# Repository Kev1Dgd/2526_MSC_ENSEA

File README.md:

# 🛠️ 2526_MSC_ENSEA — Travaux Pratiques & Projet de 3ᵉ Année

## 👋 Présentation

Bienvenue sur le dépôt GitHub regroupant **l’ensemble des travaux pratiques (TP)** et **le projet de 3ᵉ année** réalisés dans le cadre de la formation à l’[**École Nationale Supérieure de l’Électronique et de ses Applications (ENSEA)**](https://www.ensea.fr/).

Ce dépôt est maintenu par :

* **Kévin Dgd** ([Kev1Dgd](https://github.com/Kev1Dgd))
* **Elio Flandin** ([elioflandin](https://github.com/elioflandin))
* **Tristan Noterman** (projet)

---

## 🎓 Contexte académique

Nous sommes actuellement en **troisième année de la spécialité *Mécatronique et Systèmes Complexes (MSC)*** à l’ENSEA.
Cette spécialité forme des ingénieurs capables de concevoir, modéliser et piloter des systèmes intégrant à la fois des composants **mécaniques, électroniques et informatiques embarqués**.

### 🧩 Matières étudiées

Les TP et projets s’appuient sur les enseignements suivants :

* 🤖 **Robotique**
* 📡 **Capteurs et chaînes de mesure**
* 🧠 **Systèmes d’acquisition et de commande**
* ⏱️ **Noyau temps réel**
* 🔗 **Bus et réseaux**
* ✈️ **Préparation d'un drone volant à "l'infini"**

---

## 📂 Structure du dépôt

```
📦 2526_MSC_ENSEA
 ┣ 📁 Robotique_TP
 ┣ 📁 Capteurs_TP
 ┣ 📁 SystemesAcquisitionCommande_TP
 ┣ 📁 Noyau_Temps_Reel_TP
 ┣ 📁 Bus&Reseaux_TP
 ┣ 📁 Projet_Drone_Infini
 ┗ 📜 README.md
```

Chaque dossier de TP contient :

* Le code source (`.c`, `.cpp`, `.py`, `.ino`, etc.)
* Les schémas électriques / mécaniques associés
* Les rapports ou notes explicatives

---

## 🛩️ Projet de 3ᵉ année — **Planeur Énergétiquement Autonome**

### 🧠 Objectif du projet

Concevoir un **planeur miniature autonome** capable de :

* **Voler indéfiniment** sans intervention extérieure
* **Exploiter l’énergie solaire** le jour pour recharger ses batteries
* **Utiliser un moteur électrique** la nuit pour reprendre de l’altitude

### ⚙️ Aspects techniques couverts

* **Conception électronique complète (PCB)**
* **Développement embarqué (microcontrôleur, C/C++)**
* **Asservissement et contrôle en vol**
* **Gestion énergétique et supervision logicielle**

### 🧰 Technologies utilisées

* Conception PCB : *KiCad / Altium Designer*
* Microcontrôleur : *STM32 / Arduino / ESP32 (selon choix final)*
* Simulation / modélisation : *MATLAB / Simulink*
* Communication : *Bus CAN, UART, I²C*
* Langages : *C, Python, Assembly (au besoin)*

---

## 🧑‍🤝‍🧑 Équipe projet

| Nom                  | Rôle                                          | GitHub                                         |
| -------------------- | --------------------------------------------- | ---------------------------------------------- |
| **Kévin Dgd**        | Développement, intégration et électronique    | [@Kev1Dgd](https://github.com/Kev1Dgd)         |
| **Elio Flandin**     | Programmation, conception système, tests      | [@elioflandin](https://github.com/elioflandin) |
| **Tristan Noterman** | Modélisation, simulation et support technique | —                                              |

---

## 🚀 Objectif final

Créer un **système mécatronique complet**, modulaire et documenté, combinant :

* électronique embarquée,
* asservissement moteur,
* gestion énergétique intelligente,
* et communication robuste.

Le tout dans le cadre d’un **projet d’ingénierie complet**, fidèle à la démarche et aux exigences de la formation ENSEA.

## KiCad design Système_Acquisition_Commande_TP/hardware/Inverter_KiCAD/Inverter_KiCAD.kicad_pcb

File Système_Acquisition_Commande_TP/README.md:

# 🏎️ Projet MSC : Asservissement de Machine à Courant Continu (MCC)
**ENSEA 2025-2026** DUGARD Kevin & FLANDIN Elio  
**Encadrant :** Nicolas Papazoglou

---

## 📌 Présentation du Projet
Ce projet consiste à réaliser le pilotage complet d'un moteur à courant continu via un **hacheur en pont en H** et une carte **Nucleo-STM32G474RE**. 

L'objectif est d'implémenter :
1. La génération de signaux **PWM complémentaires décalés**.
2. L'acquisition de données capteurs (courant, vitesse).
3. L'asservissement en temps réel du système.

---

## 🛠️ Architecture du Logiciel
Le projet est structuré de manière modulaire pour faciliter la maintenance et la portabilité :

* **`acquisition/`** : Gestion des entrées analogiques (ADC/DMA) et des codeurs incrémentaux.
* **`motor_control/`** : Pilotage du hacheur (PWM) et algorithmes d'asservissement (PID).
* **`user_interface/`** : Interaction via le `shell` UART, gestion des LEDs et boutons.
* **`app.c`** : Point d'entrée de l'application (initialisation et boucle principale).

---

## 🚀 Fonctionnalités du Shell
Nous utilisons un terminal série (115200 baud) pour piloter le moteur en temps réel.

| Commande | Action |
| :--- | :--- |
| `help` | Affiche la liste des commandes disponibles. |
| `start` | Active les PWM et fixe le rapport cyclique à 50% (repos). |
| `stop` | Désactive immédiatement les sorties PWM. |
| `speed <val>` | Définit la vitesse cible avec une rampe d'accélération. |
| `test` | Vérifie la transmission des arguments. |

---

## 📈 État d'avancement du TP

### 1. Commande Basique (PWM)
- [x] Configuration du Timer à **20kHz**.
- [x] Insertion du **temps mort** (Deadtime) selon la datasheet.
- [x] Validation à l'oscilloscope des signaux complémentaires.
- [x] Implémentation de la rampe d'accélération pour éviter les pics de courant.

### 2. Acquisition de Données
- [ ] Mesure du courant par **ADC en mode DMA** (synchrone avec la PWM).
- [ ] Lecture de la vitesse via le **codeur incrémental**.
- [ ] Calcul de la fonction de transfert du capteur de vitesse.

### 3. Asservissement (En cours...)
- [ ] Identification de la constante de temps mécanique.
- [ ] Implémentation du correcteur PID.

---

## 🛠 Configuration Matérielle (Hardware)

### Hacheur & PWM
* **Fréquence :** 20 kHz
* **Résolution :** > 10 bits
* **Topologie :** Commande complémentaire décalée (4 transistors).

---

## 📝 Bonnes Pratiques de Code
Pour ce projet, nous respectons les règles suivantes :
* **Naming :** `snake_case` pour les variables, `UPPER_CASE` pour les macros.
* **Zéro "Nombre Magique" :** Utilisation systématique de `#define`.
* **Sécurité :** Vérification systématique du retour des fonctions HAL.
* **Modularité :** Fonctions factorisées pour éviter la duplication.

---

## ⚙️ Installation et Utilisation
1. Cloner le dépôt :
   ```bash
   git clone [https://github.com/votre_nom/2526_MSC_SAC_NOM1_NOM2.git](https://github.com/votre_nom/2526_MSC_SAC_NOM1_NOM2.git)

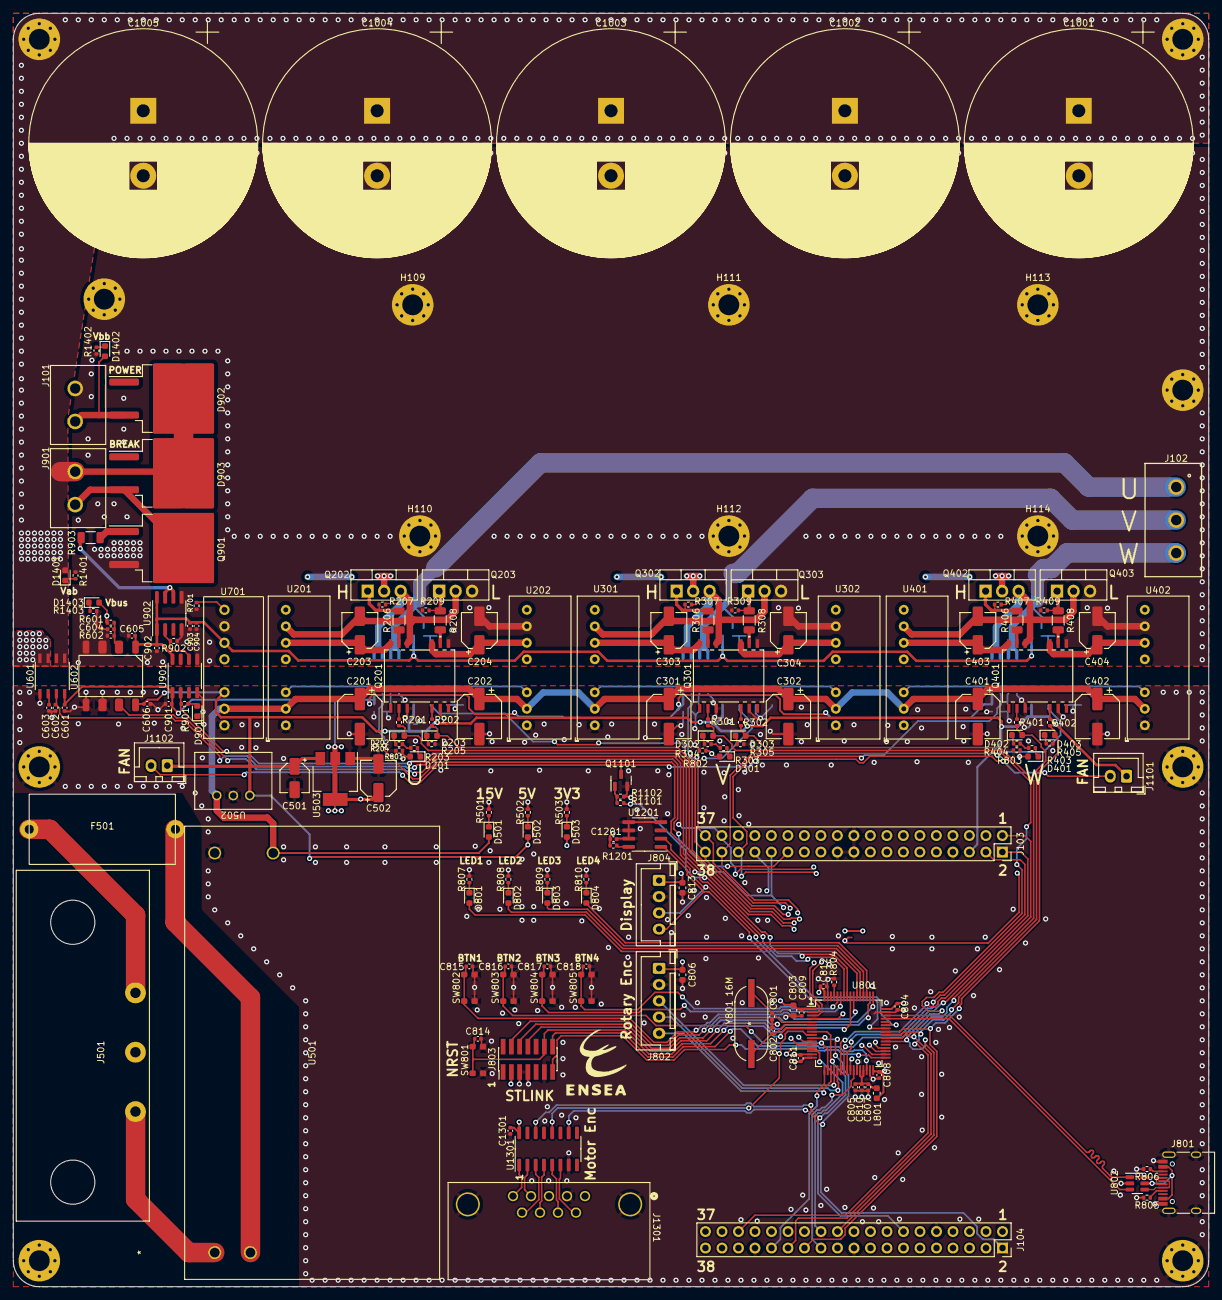
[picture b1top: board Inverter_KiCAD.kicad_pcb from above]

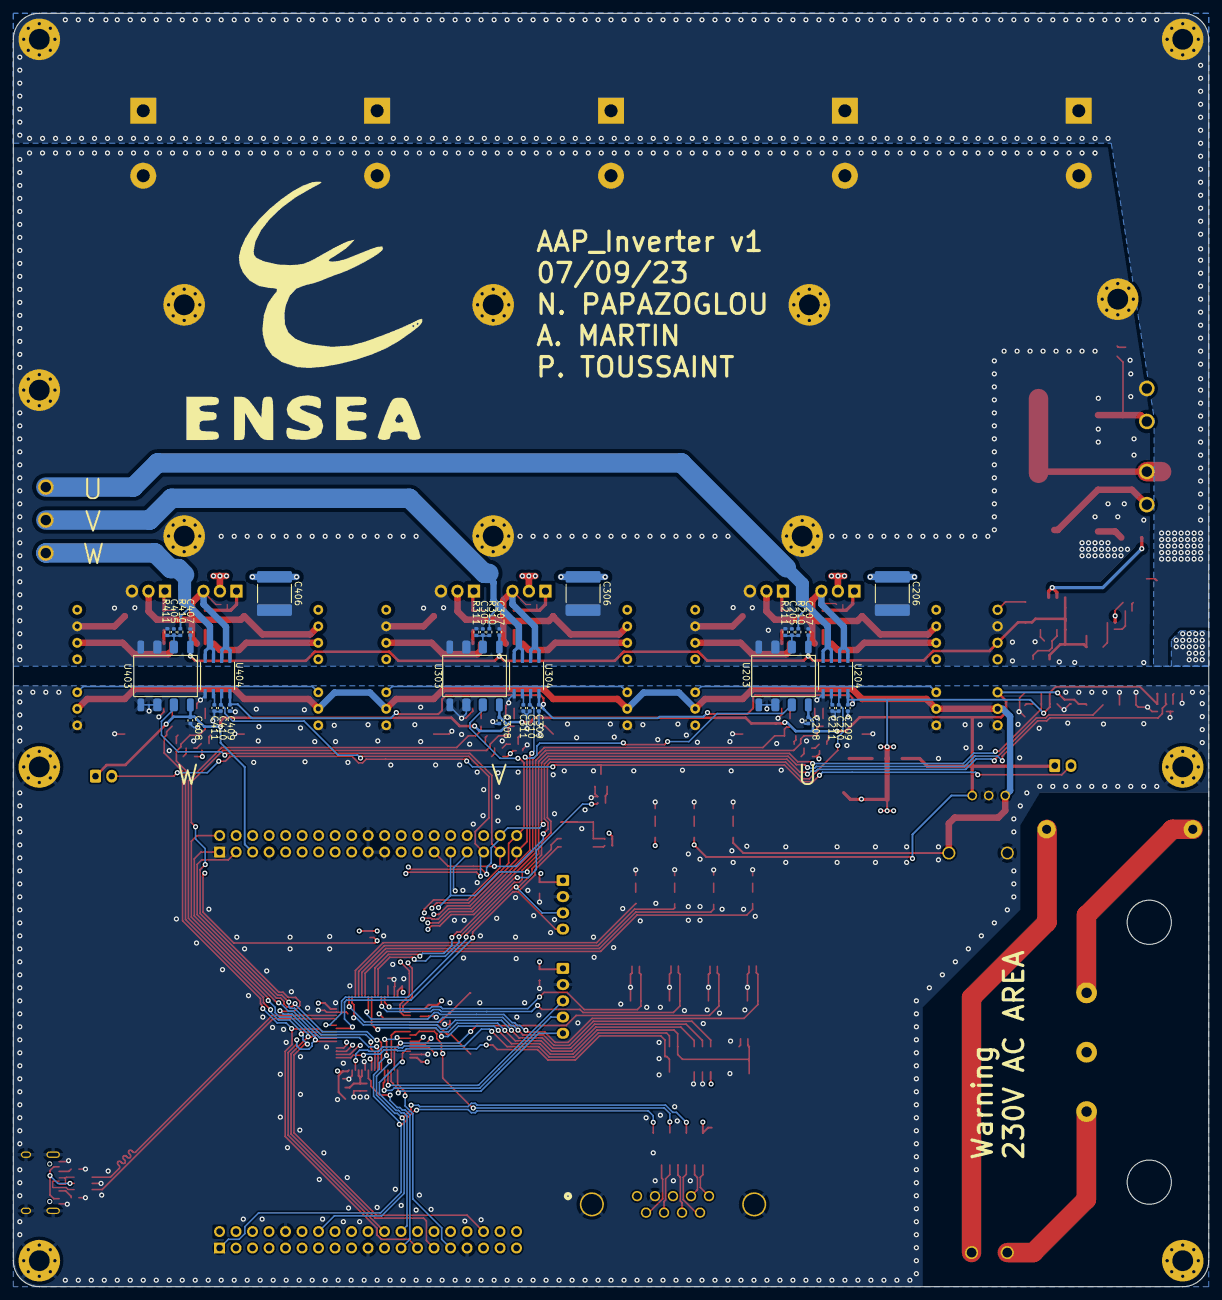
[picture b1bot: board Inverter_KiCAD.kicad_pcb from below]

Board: 4 copper layers, 184.0 x 196.0 mm, 220 parts (33 on the bottom side), 139 nets.

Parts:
C201, C202, C301, C302, C401, C402: 100u; CP_Elec_6.3x7.7
C203, C204, C303, C304, C403, C404, C502: 22u; CP_Elec_5x5.4
C205, C305, C405, C604: 10n; C_0402_1005Metric
C206, C306, C406: 10u; C_2220_5650Metric
C207, C208, C307, C308, C407, C408, C605, C606, C804, C807, C808, C809, C810, C811, C812, C814, C815, C816, C817, C818, C901, C902, C1201, C1301: 100n; C_0402_1005Metric
C209, C210, C211, C309, C310, C311, C409, C410, C411, C601, C602, C603: 4.7n; C_0402_1005Metric
C501: 10u; CP_Elec_4x5.4
C801, C802: 22p; C_0402_1005Metric
C803, C806, C813: 10u; C_0603_1608Metric
C805, C903: 1u; C_0402_1005Metric
C904: 1n; C_0402_1005Metric
C1001, C1002, C1003, C1004, C1005: 1.5m; CP_Radial_D35.0mm_P10.00mm_SnapIn
D201, D301, D401: Green LED; LED_0603_1608Metric
D202, D203, D302, D303, D402, D403, D501, D502, D503, D901, D1401, D1402, D1403: Red LED; LED_0603_1608Metric
D801, D802, D803, D804: Blue LED; LED_0603_1608Metric
D902, D903: VS-15TQ060S-M3; TO-263-2
F501: Fuse; 0031.8201
H101, H102, H103, H104, H105, H106, H107, H108, H109, H110, H111, H112, H113, H114: MountingHole_Pad; MountingHole_3.2mm_M3_Pad_Via
J101, J901: Conn_01x02; 691311500102
J102: Conn_01x03; 691311500103
J103, J104: Conn_02x19_Odd_Even; PinSocket_2x19_P2.54mm_Vertical
J501: PX0580-PC-12132
J801: USB_C_Receptacle_USB2.0; USB_C_Receptacle_HRO_TYPE-C-31-M-12
J802: Conn_01x05; JST_XH_B5B-XH-A_1x05_P2.50mm_Vertical
J803: Conn_ST_STDC14; PinHeader_2x07_P1.27mm_Vertical_SMD
J804: Conn_01x04; JST_XH_B4B-XH-A_1x04_P2.50mm_Vertical
J1101, J1102: Conn_01x02; JST_XH_B2B-XH-A_1x02_P2.50mm_Vertical
J1301: DE9_Receptacle_MountingHoles; 618009233821
L801: 39n; L_0603_1608Metric
Q201, Q301, Q401: HCPL-315J-500E; SO-16_HCPL-315J_BRA
Q202, Q203, Q302, Q303, Q402, Q403: IRF540N; TO-220-3_Vertical
Q901: BUK9637-100E; TO-263-2
Q1101: SQ2310ES; SOT-23
R201, R202, R301, R302, R401, R402: 170; R_0402_1005Metric
R203, R204, R205, R303, R304, R305, R403, R404, R405, R503, R807, R808, R809, R810, R901: 390; R_0402_1005Metric
R206, R208, R306, R308, R406, R408: 30; R_1206_3216Metric
R207, R209, R307, R309, R407, R409, R801, R802, R803, R804, R902, R1102, R1401, R1402, R1403: 10k; R_0402_1005Metric
R210, R310, R410, R601: 470k; R_0402_1005Metric
R211, R311, R411, R602: 1k; R_0402_1005Metric
R501: 2k7; R_0402_1005Metric
R502: 680; R_0402_1005Metric
R701: 27k; R_0402_1005Metric
R805, R806: 5.1k; R_0402_1005Metric
R903: 4.7; R_1206_3216Metric
R1101: 22; R_0402_1005Metric
R1201: 200; R_0402_1005Metric
SW801, SW802, SW803, SW804, SW805: SW_Push; 435451019820
U201, U202, U301, U302, U401, U402: MPRB2415S-6W; MPRB2415S
U203, U303, U403, U602: HCPL-7800-500E; DIP-8 Gull Wing
U204, U304, U404, U601: GO 10-SME/SP3; SOIC8-GO-SME&slash_SP3_LEM
U501: MP-LD30-23B12R2; MP-LD30-23B15R2
U502: 173010542; 173010578
U503: AZ1117-3.3; SOT-223-3_TabPin2
U701: 17791063215
U801: STM32G474RETx; LQFP-64_10x10mm_P0.5mm
U802: USBLC6-2SC6; SOT-23-6
U901: ACPL-077L; SO-8_3.9x4.9mm_P1.27mm
U902: TC1412; SOIC-8_3.9x4.9mm_P1.27mm
U1201: TCN75A; SOIC-8_3.9x4.9mm_P1.27mm
U1301: MAX3097ECSE+; SOIC-16_3.9x9.9mm_P1.27mm
Y801: 16M; ABLS-7.3728MHZ-CL-RESR-A-1-G-F

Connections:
/5V: C207.1, C307.1, C407.1, C605.1, C902.1, C903.1, C904.1, U203.1 (VDD1), U303.1 (VDD1), U403.1 (VDD1), U602.1 (VDD1), U701.6 (Vout), U901.8 (VDD2), U902.1 (VDD), U902.8 (VDD)
/Arm_IRF540NBbF1/ARM_OUT: C303.2, Q301.14 (VEE), Q302.3 (S), Q303.2 (D), R307.2, U301.7 (0V), U304.1 (IP+), U304.2 (IP+)
/Arm_IRF540NBbF1/Cmd_H: Q302.1 (G), R306.2, R307.1
/Arm_IRF540NBbF1/Cmd_L: Q303.1 (G), R308.2, R309.1
/Arm_IRF540NBbF1/Uref: C311.1, U304.6 (UREF)
/Arm_IRF540NBbF1/VCC_H: C303.1, Q301.16 (VCC), U301.6 (Vout)
/Arm_IRF540NBbF1/VCC_L: C304.1, Q301.11 (VCC), U302.6 (Vout)
/Arm_IRF540NBbF2/ARM_OUT: C403.2, Q401.14 (VEE), Q402.3 (S), Q403.2 (D), R407.2, U401.7 (0V), U404.1 (IP+), U404.2 (IP+)
/Arm_IRF540NBbF2/Cmd_H: Q402.1 (G), R406.2, R407.1
/Arm_IRF540NBbF2/Cmd_L: Q403.1 (G), R408.2, R409.1
/Arm_IRF540NBbF2/Uref: C411.1, U404.6 (UREF)
/Arm_IRF540NBbF2/VCC_H: C403.1, Q401.16 (VCC), U401.6 (Vout)
/Arm_IRF540NBbF2/VCC_L: C404.1, Q401.11 (VCC), U402.6 (Vout)
/Arm_IRF540NBbF/ARM_OUT: C203.2, Q201.14 (VEE), Q202.3 (S), Q203.2 (D), R207.2, U201.7 (0V), U204.1 (IP+), U204.2 (IP+)
/Arm_IRF540NBbF/Cmd_H: Q202.1 (G), R206.2, R207.1
/Arm_IRF540NBbF/Cmd_L: Q203.1 (G), R208.2, R209.1
/Arm_IRF540NBbF/Uref: C211.1, U204.6 (UREF)
/Arm_IRF540NBbF/VCC_H: C203.1, Q201.16 (VCC), U201.6 (Vout)
/Arm_IRF540NBbF/VCC_L: C204.1, Q201.11 (VCC), U202.6 (Vout)
/Bus_Imes: C602.1, J103.36, U601.7 (UOUT), U801.36 (PB14)
/Bus_V: J103.27, U602.7 (VOUT+), U801.34 (PB12)
/ENC_A: J104.14, U801.8 (PC0), U1301.14 (OutA)
/ENC_B: J103.31, U801.9 (PC1), U1301.12 (OutB)
/ENC_Z: J104.1, U801.10 (PC2), U1301.10 (OutZ)
/I2C_SCL: J804.3, U801.43 (PA9), U1201.2 (SCL)
/I2C_SDA: J804.4, U801.42 (PA8), U1201.1 (SDA)
/ISO_3V3: C209.1, C309.1, C409.1, C502.1, C601.1, C803.1, C804.1, C806.2, C808.1, C809.1, C811.1, C812.1, C813.1, C901.1, C1201.1, C1301.1, D503.2 (A), J802.1, J803.3 (VCC), J804.1, J1301.1, L801.1, R1201.2, U204.8 (UC), U304.8 (UC), U404.8 (UC), U503.2 (VO), U601.8 (UC), U801.1 (VBAT), U801.16 (VDD), U801.32 (VDD), U801.48 (VDD), U801.64 (VDD), U901.1 (VDD1), U1301.16 (VCC)
/ISO_5V: C208.1, C308.1, C408.1, C501.1, C606.1, D502.2 (A), J103.5, J1101.1, J1102.1, U203.8 (VDD2), U303.8 (VDD2), U403.8 (VDD2), U502.3 (5V), U503.3 (VI), U602.8 (VDD2), U701.3 (Ctrl)
/ISO_15V: C201.1, C202.1, C301.1, C302.1, C401.1, C402.1, D501.2 (A), U201.2 (Vin), U202.2 (Vin), U301.2 (Vin), U302.2 (Vin), U401.2 (Vin), U402.2 (Vin), U501.3 (+15V), U502.1 (VIN), U701.2 (Vin)
/ISO_GND: C201.2, C202.2, C208.2, C209.2, C210.2, C211.2, C301.2, C302.2, C308.2, C309.2, C310.2, C311.2, C401.2, C402.2, C408.2, C409.2, C410.2, C411.2, C501.2, C502.2, C601.2, C602.2, C603.2, C606.2, C801.1, C802.1, C803.2, C804.2, C805.2, C806.1, C807.2, C808.2, C809.2, C810.2, C811.2, C812.2, C813.2, C814.2, C815.2, C816.2, C817.2, C818.2, C901.2, C1201.2, C1301.2, D901.1 (K), H102.1, H103.1, H104.1, J103.7, J103.19, J103.20, J103.21, J104.10, J104.19, J104.31, J801.A1 (GND), J801.A12 (GND), J801.B1 (GND), J801.B12 (GND), J801.S1 (SHIELD), J802.2, J803.5 (GND), J803.7 (GND), J803.11 (GNDDetect), J804.2, J1301.2, J1301.10 (PAD), Q201.3 (Cathode), Q201.7 (Cathode), Q301.3 (Cathode), Q301.7 (Cathode), Q401.3 (Cathode), Q401.7 (Cathode), Q1101.2 (S), R203.2, R204.2, R205.2, R303.2, R304.2, R305.2, R403.2, R404.2, R405.2, R501.2, R502.2, R503.2, R801.2, R802.2, R803.2, R804.2, R805.2, R806.2, R807.2, R808.2, R809.2, R810.2, R1102.2, SW801.2, SW802.2, SW803.2, SW804.2, SW805.2, U201.1 (GND), U202.1 (GND), U203.5 (GND2), U203.6 (VOUT-), U204.5 (GND), U301.1 (GND), U302.1 (GND), U303.5 (GND2), U303.6 (VOUT-), U304.5 (GND), U401.1 (GND), U402.1 (GND), U403.5 (GND2), U403.6 (VOUT-), U404.5 (GND), U501.4 (GND), U502.2 (GND), U503.1 (GND), U601.5 (GND), U602.5 (GND2), U602.6 (VOUT-), U701.1 (Vin_GND), U801.15 (VSS), U801.27 (VSSA), U801.31 (VSS), U801.47 (VSS), U801.63 (VSS), U802.2 (GND), U901.4 (GND1), U1201.4 (GND), U1201.5 (A2), U1201.6 (A1), U1201.7 (A0), U1301.7 (GND)
/ISO_PWM_Break: R901.1, U801.58 (PB5), U901.2 (In)
/ISO_PWM_FAN: R1101.2, U801.57 (PB4)
/MCU_STM32G474/D+: J801.A6 (D+), J801.B6 (D+), U802.6 (I/O1)
/MCU_STM32G474/D-: J801.A7 (D-), J801.B7 (D-), U802.4 (I/O2)
/MCU_STM32G474/ENC_BTN_A: J802.3, U801.20 (PA6)
/MCU_STM32G474/ENC_BTN_B: J802.4, U801.21 (PA7)
/MCU_STM32G474/ENC_BTN_P: J802.5, U801.19 (PA5)
/MCU_STM32G474/ISO_3V3A: C805.1, C807.1, C810.1, L801.2, U801.28 (VREF+), U801.29 (VDDA)
/MCU_STM32G474/NRST: C814.1, J803.12 (~RST), SW801.1, U801.7 (PG10)
/MCU_STM32G474/SWCLK: J803.6 (JCLK/SWCLK), U801.50 (PA14)
/MCU_STM32G474/SWDIO: J803.4 (JTMS/SWDIO), U801.49 (PA13)
/MCU_STM32G474/SWO: J803.8 (JTDO/SWO), U801.56 (PB3)
/MCU_STM32G474/Soft_NRST: C818.1, SW805.1, U801.60 (PB7)
/MCU_STM32G474/USB_DM: U801.45 (PA11), U802.3 (I/O2)
/MCU_STM32G474/USB_DP: U801.46 (PA12), U802.1 (I/O1)
/MCU_STM32G474/USR_BTN_1: C815.1, SW802.1, U801.55 (PD2)
/MCU_STM32G474/USR_BTN_2: C816.1, SW803.1, U801.18 (PA4)
/MCU_STM32G474/USR_BTN_3: C817.1, SW804.1, U801.59 (PB6)
/MCU_STM32G474/USR_LED_1: D801.2 (A), U801.54 (PC12)
/MCU_STM32G474/USR_LED_2: D802.2 (A), U801.53 (PC11)
/MCU_STM32G474/USR_LED_3: D803.2 (A), U801.52 (PC10)
/MCU_STM32G474/USR_LED_4: D804.2 (A), U801.51 (PA15)
/MCU_STM32G474/VCP_RX: J803.13 (VCP_RX), U801.33 (PB11)
/MCU_STM32G474/VCP_TX: J803.14 (VCP_TX), U801.30 (PB10)
/MCU_STM32G474/V_USB: J801.A4 (VBUS), J801.A9 (VBUS), J801.B4 (VBUS), J801.B9 (VBUS), U802.5 (VBUS)
/NUCLEO_NRST: J103.3, U801.24 (PB0)
/NUCLEO_RX: J103.1, U801.22 (PC4)
/NUCLEO_TX: J103.2, U801.23 (PC5)
/Pwr_En_U: D201.2 (A), R801.1, U201.3 (Ctrl), U202.3 (Ctrl), U801.2 (PC13)
/Pwr_En_V: D301.2 (A), R802.1, U301.3 (Ctrl), U302.3 (Ctrl), U801.3 (PC14)
/Pwr_En_W: D401.2 (A), R803.1, U401.3 (Ctrl), U402.3 (Ctrl), U801.4 (PC15)
/U_Imes: C210.1, J103.29, U204.7 (UOUT), U801.13 (PA1)
/U_PWM_H: D202.2 (A), J104.24, R201.2, U801.14 (PA2)
/U_PWM_L: D203.2 (A), J104.29, R202.2, U801.17 (PA3)
/U_VPh: J103.37, U203.7 (VOUT+), U801.12 (PA0)
/U_output: J102.1, R210.1, U204.3 (IP-), U204.4 (IP-)
/VSupply_AB: C1001.1, C1002.1, C1003.1, C1004.1, C1005.1, D902.2 (K), D903.2 (K), D1401.2 (A), H107.1, H108.1, J901.2, U601.1 (IP+), U601.2 (IP+)
/VSupply_BB: D902.3 (A), D1402.2 (A), J101.1
/V_Imes: C310.1, J104.23, U304.7 (UOUT), U801.26 (PB2)
/V_PWM_H: D302.2 (A), J104.22, R301.2, U801.38 (PC6)
/V_PWM_L: D303.2 (A), J104.27, R302.2, U801.39 (PC7)
/V_VPh: J103.38, U303.7 (VOUT+), U801.11 (PC3)
/V_output: J102.2, R310.1, U304.3 (IP-), U304.4 (IP-)
/Vbus: C206.1, C306.1, C406.1, D1403.2 (A), Q202.2 (D), Q302.2 (D), Q402.2 (D), R601.1, U601.3 (IP-), U601.4 (IP-)
/Vbus_Sense/Uref: C603.1, U601.6 (UREF)
/W_Imes: C410.1, J103.33, U404.7 (UOUT), U801.35 (PB13)
/W_PWM_H: D402.2 (A), J104.34, R401.2, U801.40 (PC8)
/W_PWM_L: D403.2 (A), J104.25, R402.2, U801.41 (PC9)
/W_VPh: J103.35, U403.7 (VOUT+), U801.25 (PB1)
/W_output: J102.3, R410.1, U404.3 (IP-), U404.4 (IP-)
/break/Break_Drain_Mosfet: D903.3 (A), J901.1, Q901.2 (D)
/break/PWM_Break: R902.1, U901.6 (Out), U902.2 (IN)
/break/PWM_Mosfet: R903.1, U902.6 (OUT), U902.7 (OUT)
/encoderMotor/A: J1301.5, U1301.1 (A)
/encoderMotor/B: J1301.9, U1301.3 (B)
/encoderMotor/Z: J1301.7, U1301.5 (Z)
/encoderMotor//A: J1301.4, U1301.2 (/A)
/encoderMotor//B: J1301.8, U1301.4 (/B)
/encoderMotor//Z: J1301.6, U1301.6 (/Z)
GND: C204.2, C205.2, C206.2, C207.2, C304.2, C305.2, C306.2, C307.2, C404.2, C405.2, C406.2, C407.2, C604.2, C605.2, C902.2, C903.2, C904.2, C1001.2, C1002.2, C1003.2, C1004.2, C1005.2, H105.1, H106.1, H109.1, H110.1, H111.1, H112.1, H113.1, H114.1, J101.2, Q201.9 (VEE), Q203.3 (S), Q301.9 (VEE), Q303.3 (S), Q401.9 (VEE), Q403.3 (S), Q901.3 (S), R209.2, R211.2, R309.2, R311.2, R409.2, R411.2, R602.2, R701.2, R902.2, R1401.2, R1402.2, R1403.2, U202.7 (0V), U203.3 (VIN-), U203.4 (GND1), U302.7 (0V), U303.3 (VIN-), U303.4 (GND1), U402.7 (0V), U403.3 (VIN-), U403.4 (GND1), U602.3 (VIN-), U602.4 (GND1), U701.7 (Vout_Gnd), U901.5 (GND2), U902.4 (GND), U902.5 (GND)
unnamed: D201.1 (K), R203.1
unnamed: D202.1 (K), R204.1
unnamed: D203.1 (K), R205.1
unnamed: D301.1 (K), R303.1
unnamed: D302.1 (K), R304.1
unnamed: D303.1 (K), R305.1
unnamed: D401.1 (K), R403.1
unnamed: D402.1 (K), R404.1
unnamed: D403.1 (K), R405.1
unnamed: D501.1 (K), R501.1
unnamed: D502.1 (K), R502.1
unnamed: D503.1 (K), R503.1
unnamed: D801.1 (K), R807.1
unnamed: D802.1 (K), R808.1
unnamed: D803.1 (K), R809.1
unnamed: D804.1 (K), R810.1
unnamed: D901.2 (A), R901.2
unnamed: D1401.1 (K), R1401.1
unnamed: D1402.1 (K), R1402.1
unnamed: D1403.1 (K), R1403.1
unnamed: F501.1, J501.3 (L)
unnamed: J501.1 (N), U501.1 (AC(L))
unnamed: J801.A5 (CC1), R805.1
unnamed: J801.B5 (CC2), R806.1
unnamed: J1101.2, J1102.2, Q1101.3 (D)
unnamed: Q201.2 (Anode), R201.1
unnamed: Q201.6 (Anode), R202.1
unnamed: Q201.10 (Vo), R208.1
unnamed: Q201.15 (Vo), R206.1
unnamed: Q301.2 (Anode), R301.1
unnamed: Q301.6 (Anode), R302.1
unnamed: Q301.10 (Vo), R308.1
unnamed: Q301.15 (Vo), R306.1
unnamed: Q401.2 (Anode), R401.1
unnamed: Q401.6 (Anode), R402.1
unnamed: Q401.10 (Vo), R408.1
unnamed: Q401.15 (Vo), R406.1
unnamed: Q901.1 (G), R903.2
unnamed: Q1101.1 (G), R1101.1, R1102.1
unnamed: C205.1, R210.2, R211.1, U203.2 (VIN+)
unnamed: C305.1, R310.2, R311.1, U303.2 (VIN+)
unnamed: C405.1, R410.2, R411.1, U403.2 (VIN+)
unnamed: F501.2, U501.2 (AC(N))
unnamed: C604.1, R601.2, R602.1, U602.2 (VIN+)
unnamed: R701.1, U701.8 (FB)
unnamed: R804.1, U801.61 (PB8)
unnamed: C801.2, U801.5 (PF0), Y801.2
unnamed: C802.2, U801.6 (PF1), Y801.1
unnamed: R1201.1, U1201.8 (VDD)

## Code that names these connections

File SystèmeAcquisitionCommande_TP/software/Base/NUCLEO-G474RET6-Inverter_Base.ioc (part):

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Mcu.Name=STM32G474R(B-C-E)Tx
Mcu.Package=LQFP64
Mcu.UserName=STM32G474RETx
PA0.GPIOParameters=GPIO_Label
PA0.GPIO_Label=Bus_V
PA0.Mode=IN1-Single-Ended
PA0.Signal=ADC2_IN1
PA1.GPIOParameters=GPIO_Label
PA1.GPIO_Label=U_Imes
PA1.Mode=IN2-Single-Ended
PA1.Signal=ADC1_IN2
PA10.GPIOParameters=GPIO_Label
PA10.GPIO_Label=W_PWM_H
PA10.Signal=S_TIM1_CH3
PA13.GPIOParameters=GPIO_Label
PA13.GPIO_Label=T_SWDIO
PA13.Mode=Trace_Asynchronous_SW
PA13.Signal=SYS_JTMS-SWDIO
PA14.GPIOParameters=GPIO_Label
PA14.GPIO_Label=T_SWCLK
PA14.Mode=Trace_Asynchronous_SW
PA14.Signal=SYS_JTCK-SWCLK
PA2.Mode=Asynchronous
PA2.Signal=USART2_TX
PA3.Mode=Asynchronous
PA3.Signal=USART2_RX
PA4.Signal=S_TIM3_CH2
PA5.GPIOParameters=GPIO_Label
PA5.GPIO_Label=USR_LED
PA5.Signal=GPIO_Output
PA6.Signal=S_TIM3_CH1
PA8.GPIOParameters=GPIO_Label
PA8.GPIO_Label=U_PWM_H
PA8.Signal=S_TIM1_CH1
PA9.GPIOParameters=GPIO_Label
PA9.GPIO_Label=V_PWM_H
PA9.Signal=S_TIM1_CH2
PB0.Mode=IN15-Single-Ended
PB0.Signal=ADC1_IN15
PB1.Mode=IN12-Single-Ended
PB1.Signal=ADC1_IN12
PB13.GPIOParameters=GPIO_Label
PB13.GPIO_Label=U_PWM_L
PB13.Mode=PWM Generation1 CH1 CH1N
PB13.Signal=TIM1_CH1N
PB14.GPIOParameters=GPIO_Label
PB14.GPIO_Label=V_PWM_L
PB14.Mode=PWM Generation2 CH2 CH2N
PB14.Signal=TIM1_CH2N
PB15.GPIOParameters=GPIO_Label
PB15.GPIO_Label=W_PWM_L
PB15.Mode=PWM Generation3 CH3 CH3N
PB15.Signal=TIM1_CH3N
PB3.GPIOParameters=GPIO_Label
PB3.GPIO_Label=T_SWO
PB3.Mode=Trace_Asynchronous_SW
PB3.Signal=SYS_JTDO-SWO
PC0.GPIOParameters=GPIO_Label
PC0.GPIO_Label=U_VPh
PC0.Mode=IN6-Single-Ended
PC0.Signal=ADC2_IN6
PC1.GPIOParameters=GPIO_Label
PC1.GPIO_Label=W_VPh
PC1.Mode=IN7-Single-Ended
PC1.Signal=ADC2_IN7
PC10.Mode=Asynchronous
PC10.Signal=USART3_TX
PC11.Mode=Asynchronous
PC11.Signal=USART3_RX
PC13.GPIOParameters=GPIO_Label
PC13.GPIO_Label=USR_BTN
PC13.Signal=GPXTI13
PC14-OSC32_IN.Mode=LSE-External-Oscillator
PC14-OSC32_IN.Signal=RCC_OSC32_IN
PC15-OSC32_OUT.Mode=LSE-External-Oscillator
PC15-OSC32_OUT.Signal=RCC_OSC32_OUT
PC2.GPIOParameters=GPIO_Label
PC2.GPIO_Label=Bus_Imes
PC2.Mode=IN8-Single-Ended
PC2.Signal=ADC1_IN8
PC3.GPIOParameters=GPIO_Label
PC3.GPIO_Label=V_VPh
PC3.Mode=IN9-Single-Ended
PC3.Signal=ADC2_IN9
PC8.Signal=S_TIM3_CH3
PD2.GPIOParameters=GPIO_Label
PD2.GPIO_Label=NRST_SafetyUC
PD2.Signal=GPIO_Output
PF0-OSC_IN.Mode=HSE-External-Oscillator
PF0-OSC_IN.Signal=RCC_OSC_IN
PF1-OSC_OUT.Mode=HSE-External-Oscillator
PF1-OSC_OUT.Signal=RCC_OSC_OUT
RCC.HSE_VALUE=24000000
RCC.SYSCLKFreq_VALUE=170000000
RCC.SYSCLKSource=RCC_SYSCLKSOURCE_PLLCLK
board=NUCLEO-G474RE
boardIOC=true

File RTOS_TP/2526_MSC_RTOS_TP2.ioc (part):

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Mcu.Name=STM32G431R(6-8-B)Tx
Mcu.Package=LQFP64
Mcu.UserName=STM32G431RBTx
PA13.GPIOParameters=GPIO_Label
PA13.GPIO_Label=T_SWDIO
PA13.Signal=SYS_JTMS-SWDIO
PA14.GPIOParameters=GPIO_Label
PA14.GPIO_Label=T_SWCLK
PA14.Signal=SYS_JTCK-SWCLK
PA15.Signal=GPIO_Output
PA2.GPIOParameters=GPIO_Label
PA2.GPIO_Label=LPUART1_TX [STLINKV3E_VCP_RX]
PA2.Mode=Asynchronous
PA2.Signal=LPUART1_TX
PA3.GPIOParameters=GPIO_Label
PA3.GPIO_Label=LPUART1_RX [STLINKV3E_VCP_TX]
PA3.Mode=Asynchronous
PA3.Signal=LPUART1_RX
PA5.GPIOParameters=GPIO_Label
PA5.GPIO_Label=LD2 [green]
PA5.Signal=GPIO_Output
PB3.Mode=Full_Duplex_Master
PB3.Signal=SPI3_SCK
PB4.Mode=Full_Duplex_Master
PB4.Signal=SPI3_MISO
PB5.Mode=Full_Duplex_Master
PB5.Signal=SPI3_MOSI
PB6.GPIOParameters=GPIO_Label
PB6.GPIO_Label=NSS
PB6.Signal=GPIO_Output
PB7.GPIOParameters=GPIO_Label
PB7.GPIO_Label=INT
PB7.Signal=GPXTI7
PC13.GPIOParameters=GPIO_Label
PC13.GPIO_Label=B1 [blue push button]
PC13.Signal=GPXTI13
PC14-OSC32_IN.GPIOParameters=GPIO_Label
PC14-OSC32_IN.GPIO_Label=RCC_OSC32_OUT
PC14-OSC32_IN.Signal=RCC_OSC32_IN
PC15-OSC32_OUT.GPIOParameters=GPIO_Label
PC15-OSC32_OUT.GPIO_Label=RCC_OSC32_OUT
PC15-OSC32_OUT.Signal=RCC_OSC32_OUT
PF0-OSC_IN.GPIOParameters=GPIO_Label
PF0-OSC_IN.GPIO_Label=RCC_OSC_IN
PF0-OSC_IN.Signal=RCC_OSC_IN
PF1-OSC_OUT.GPIOParameters=GPIO_Label
PF1-OSC_OUT.GPIO_Label=RCC_OSC_OUT
PF1-OSC_OUT.Signal=RCC_OSC_OUT
RCC.HSE_VALUE=24000000
RCC.SYSCLKFreq_VALUE=170000000
RCC.SYSCLKSource=RCC_SYSCLKSOURCE_PLLCLK
board=NUCLEO-G431RB
boardIOC=true

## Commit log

2025-10-23 Premier commit, github de troisième année ENSEA
2025-10-23 Revise README for project overview and team details
    Updated README.md to provide detailed project information and team roles.
2025-10-24 TP Robotique
2025-10-24 Robotique & Bus&Reseau Readmes
2025-10-24 Rename Readme.md to README.md
2025-10-24 Organizing folder for reports
2025-11-03 Architecture
2025-11-11 TP Capteurs, livrable 3
2025-11-11 Report
2025-11-15 TP3 Push + Compass start
2025-11-22 Last commit
2025-11-22 Add ReadMe
2025-11-22 Add ReadMe + Report
2025-11-23 PDF doxygen and .elf
2026-01-13 Systemes d'Acquisition et de Commande
2026-01-13 Revise topics and folder names in README
    Updated course topics and repository structure in README.
2026-01-13 Renaming Folder
2026-01-13 depot TP RTOS
2026-01-18 Revise README for MCC project overview and details
    Updated project details, structure, and features in README.
